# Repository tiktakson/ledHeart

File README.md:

# ledHeart
Simple led rgb light

Has a few modes, button feedback via vibration, also a way to control through wifi

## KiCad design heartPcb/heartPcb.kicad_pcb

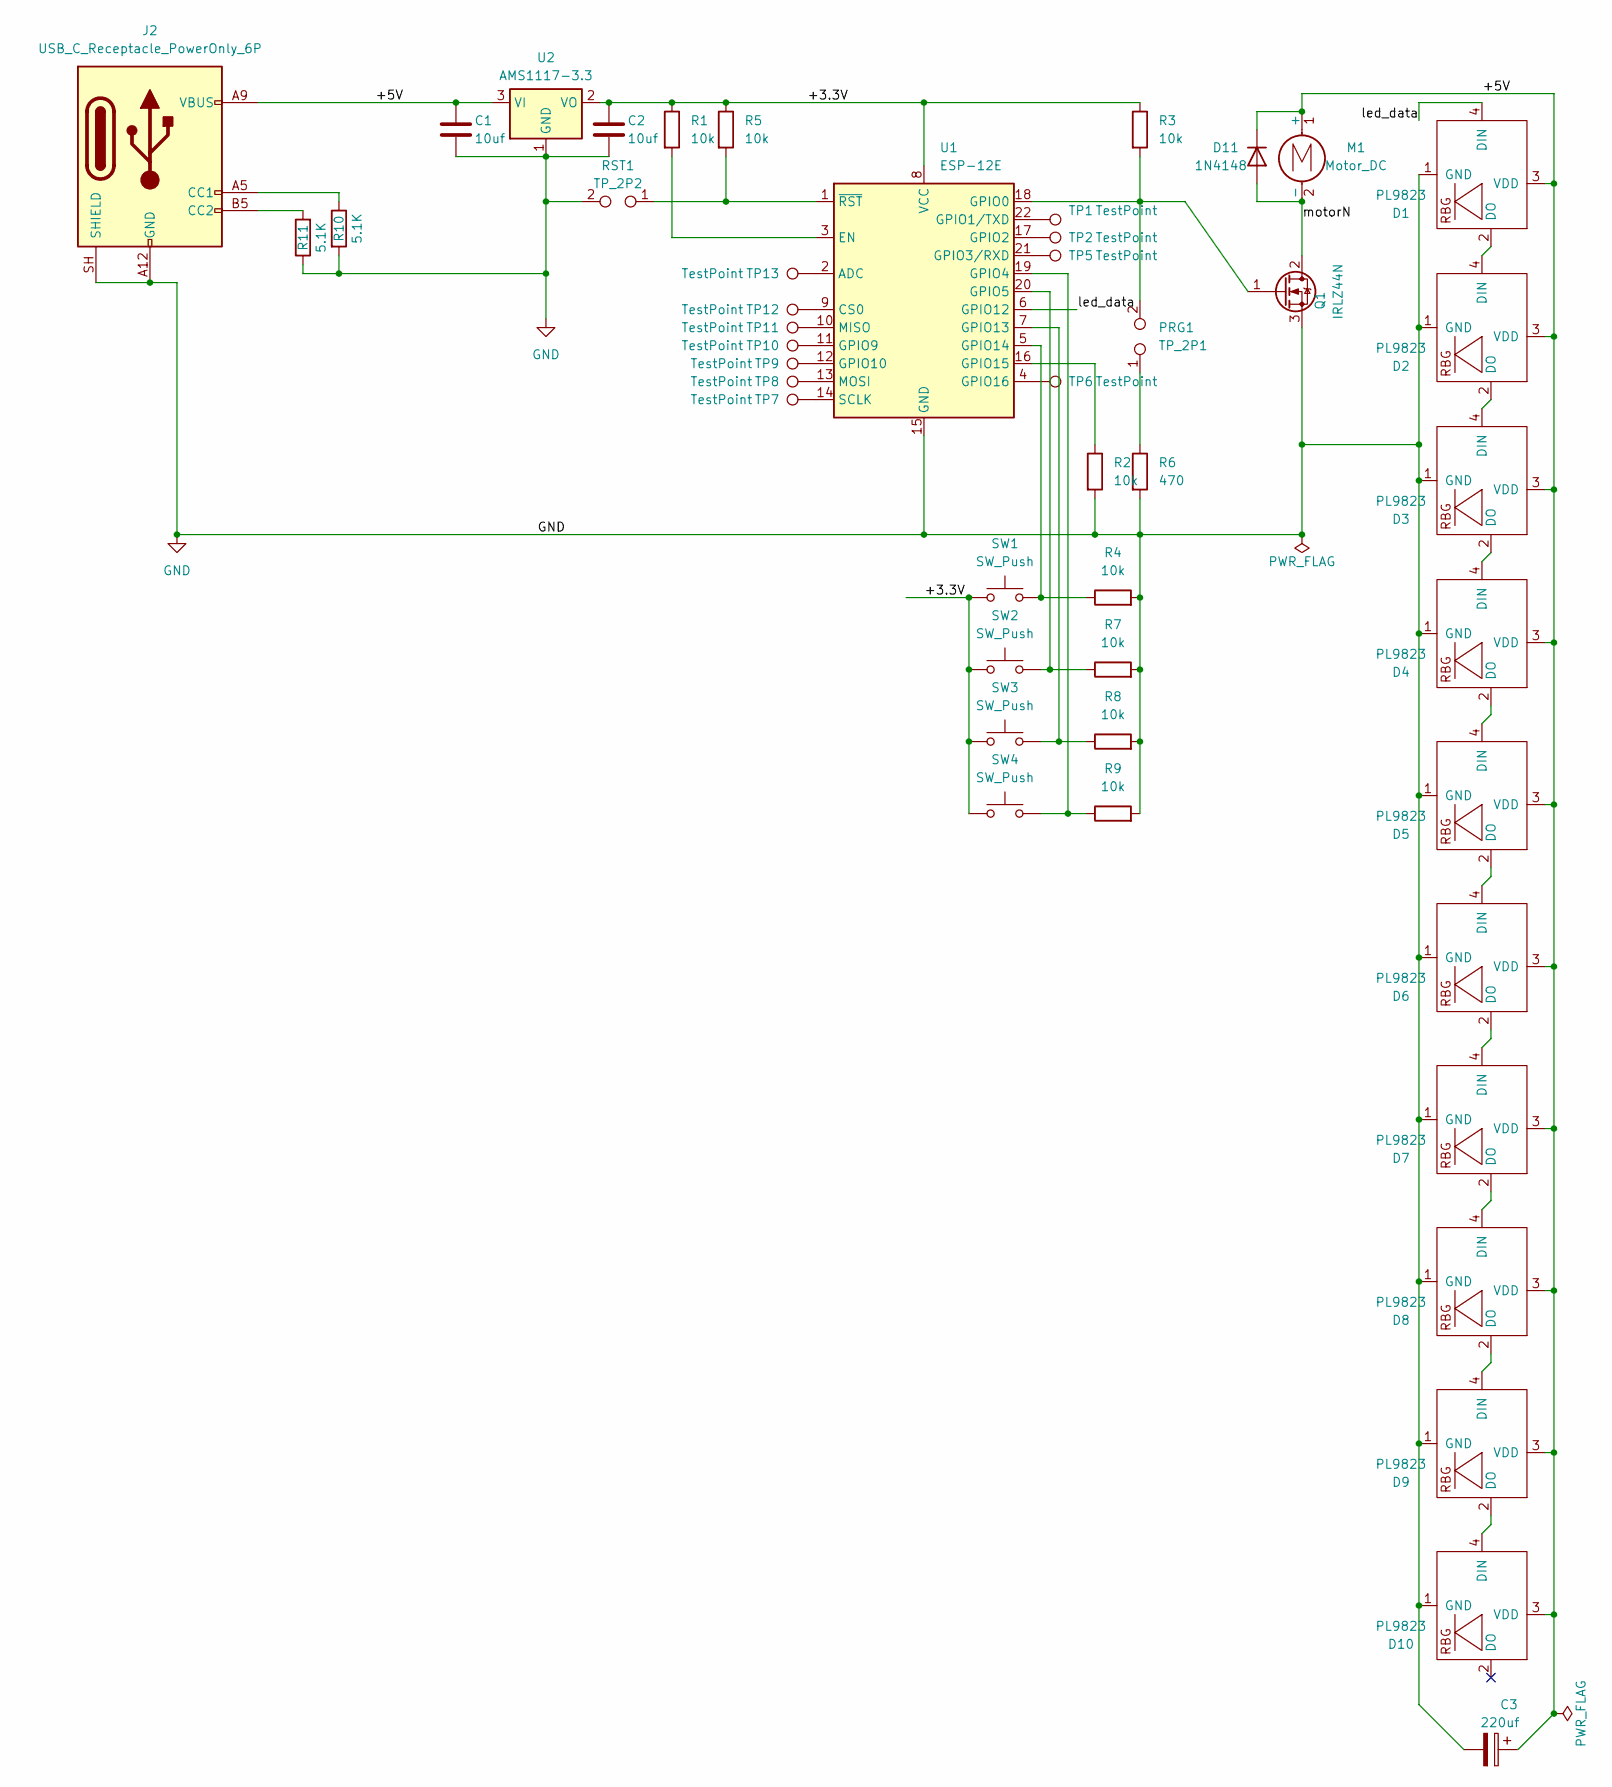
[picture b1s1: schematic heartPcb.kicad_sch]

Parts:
C1, C2: 10uf; C_0805_2012Metric_Pad1.18x1.45mm_HandSolder
C3: 220uf; CP_Radial_D8.0mm_P3.80mm
D1, D2, D3, D4, D5, D6, D7, D8, D9, D10: PL9823; pl9823n
D11: 1N4148; D_DO-35_SOD27_P7.62mm_Horizontal
J2: USB_C_Receptacle_PowerOnly_6P; USB_C_Receptacle_GCT_USB4125-xx-x-0190_6P_TopMnt_Horizontal
M1: Motor_DC; Vybronics_VZ30C1T8219732L
PRG1: TP_2P1; TestPoint_2Pads_Pitch2.54mm_Drill0.8mm
Q1: IRLZ44N; TO-220-3_Horizontal_TabDown
R1, R2, R3, R4, R5, R7, R8, R9: 10k; R_Axial_DIN0204_L3.6mm_D1.6mm_P5.08mm_Horizontal
R6: 470; R_Axial_DIN0204_L3.6mm_D1.6mm_P5.08mm_Horizontal
R10, R11: 5.1K; R_Axial_DIN0204_L3.6mm_D1.6mm_P5.08mm_Horizontal
RST1: TP_2P2; TestPoint_2Pads_Pitch2.54mm_Drill0.8mm
SW1, SW2, SW3, SW4: SW_Push; SW_PUSH_6mm_H5mm
TP1, TP2, TP5, TP6, TP7, TP8, TP9, TP10, TP11, TP12, TP13: TestPoint; TestPoint_THTPad_D1.5mm_Drill0.7mm
U1: ESP-12E
U2: AMS1117-3.3; SOT-223-3_TabPin2

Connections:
/+3.3V: C2.1, R1.1, R3.1, R5.1, SW1.1, SW2.1, SW3.1, SW4.1, U1.8 (VCC), U2.2 (VO)
/+5V: C1.1, C3.1, D1.3 (VDD), D2.3 (VDD), D3.3 (VDD), D4.3 (VDD), D5.3 (VDD), D6.3 (VDD), D7.3 (VDD), D8.3 (VDD), D9.3 (VDD), D10.3 (VDD), D11.1 (K), J2.A9 (VBUS), J2.B9 (VBUS), M1.1 (+), U2.3 (VI)
/led_data: D1.4 (DIN), U1.6 (GPIO12)
/motorN: D11.2 (A), M1.2 (-), Q1.2 (D)
GND: C1.2, C2.2, C3.2, D1.1 (GND), D2.1 (GND), D3.1 (GND), D4.1 (GND), D5.1 (GND), D6.1 (GND), D7.1 (GND), D8.1 (GND), D9.1 (GND), D10.1 (GND), J2.A12 (GND), J2.B12 (GND), J2.SH (SHIELD), Q1.3 (S), R2.2, R4.2, R6.2, R7.2, R8.2, R9.2, R10.2, R11.1, RST1.2, U1.15 (GND), U2.1 (GND)
unnamed: D1.2 (DO), D2.4 (DIN)
unnamed: D2.2 (DO), D3.4 (DIN)
unnamed: D3.2 (DO), D4.4 (DIN)
unnamed: D4.2 (DO), D5.4 (DIN)
unnamed: D5.2 (DO), D6.4 (DIN)
unnamed: D6.2 (DO), D7.4 (DIN)
unnamed: D7.2 (DO), D8.4 (DIN)
unnamed: D8.2 (DO), D9.4 (DIN)
unnamed: D9.2 (DO), D10.4 (DIN)
unnamed: J2.A5 (CC1), R10.1
unnamed: J2.B5 (CC2), R11.2
unnamed: PRG1.1, R6.1
unnamed: PRG1.2, Q1.1 (G), R3.2, U1.18 (GPIO0)
unnamed: TP13.1 (1_1), U1.2 (ADC)
unnamed: TP12.1 (1_1), U1.9 (CS0)
unnamed: R1.2, U1.3 (EN)
unnamed: TP1.1 (1_1), U1.22 (GPIO1/TXD)
unnamed: TP2.1 (1_1), U1.17 (GPIO2)
unnamed: TP5.1 (1_1), U1.21 (GPIO3/RXD)
unnamed: R9.1, SW4.2, U1.19 (GPIO4)
unnamed: R7.1, SW2.2, U1.20 (GPIO5)
unnamed: TP10.1 (1_1), U1.11 (GPIO9)
unnamed: TP9.1 (1_1), U1.12 (GPIO10)
unnamed: R8.1, SW3.2, U1.7 (GPIO13)
unnamed: R4.1, SW1.2, U1.5 (GPIO14)
unnamed: R2.1, U1.16 (GPIO15)
unnamed: TP6.1 (1_1), U1.4 (GPIO16)
unnamed: TP11.1 (1_1), U1.10 (MISO)
unnamed: TP8.1 (1_1), U1.13 (MOSI)
unnamed: TP7.1 (1_1), U1.14 (SCLK)
unnamed: R5.2, RST1.1, U1.1 (~RST)

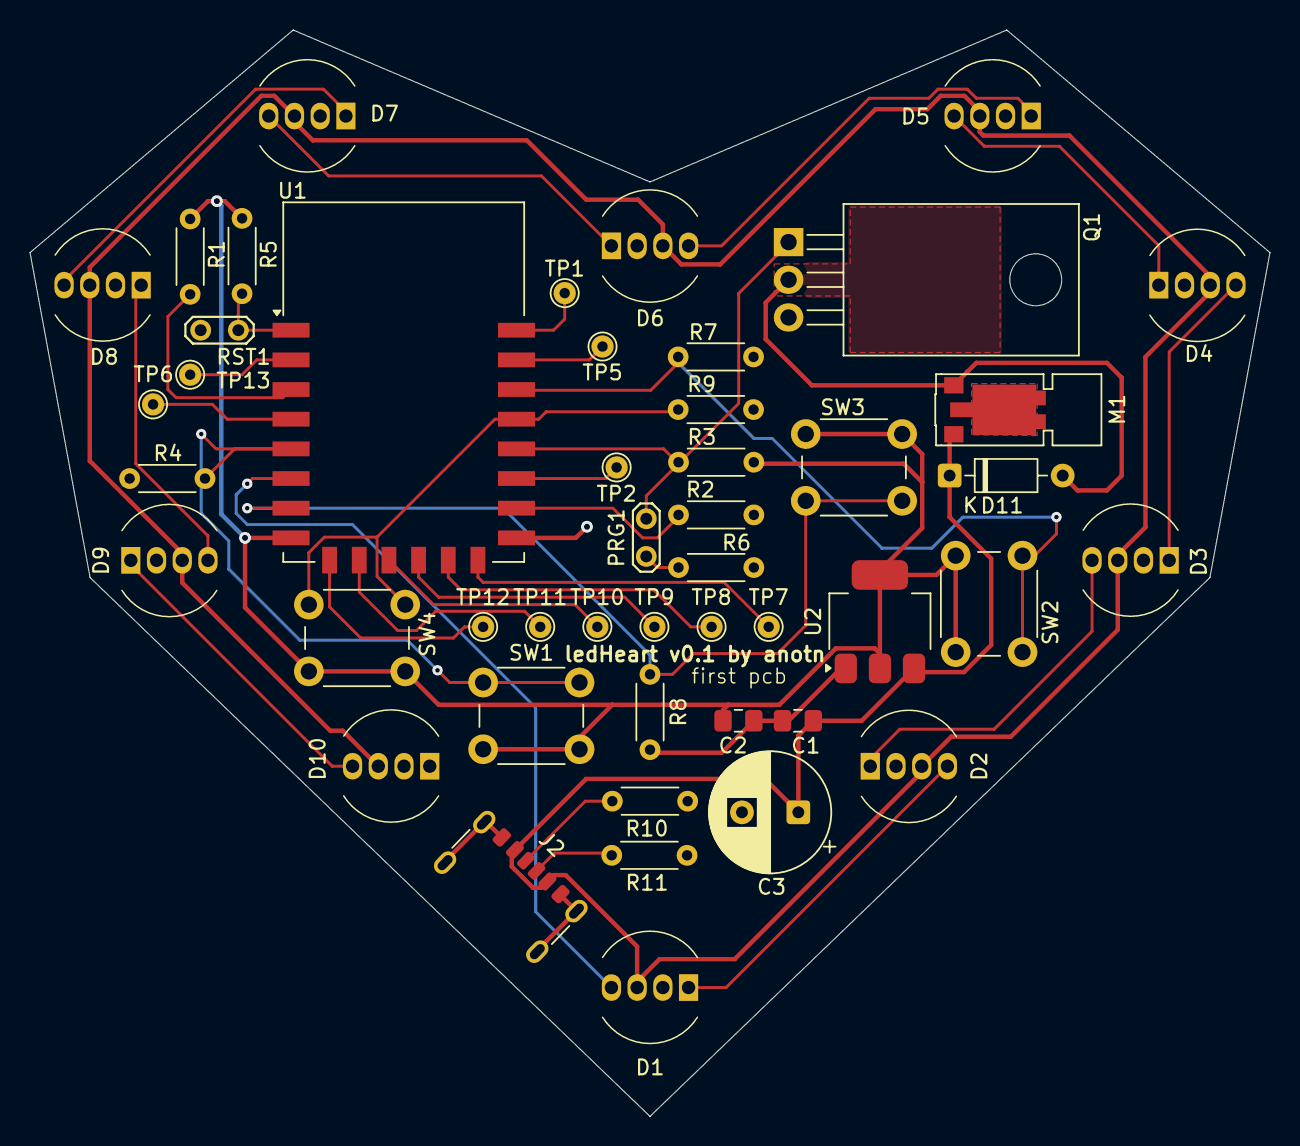
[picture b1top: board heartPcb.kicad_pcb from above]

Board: 2 copper layers, 83.6 x 73.2 mm, 47 parts (0 on the bottom side), 36 nets.
